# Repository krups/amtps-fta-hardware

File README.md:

# amtps-fta
Design files for the additive manufacturing thermal of thermal protection systems (AMTPS) flight test article (FTA)

See [documentation/amtps-fta-harware-manual.pdf](documentation/amtps-fta-harware-manual.pdf)

For an overview of the work, see the presentation here [documentation/presentation.pdf](documentation/presentation.pdf)

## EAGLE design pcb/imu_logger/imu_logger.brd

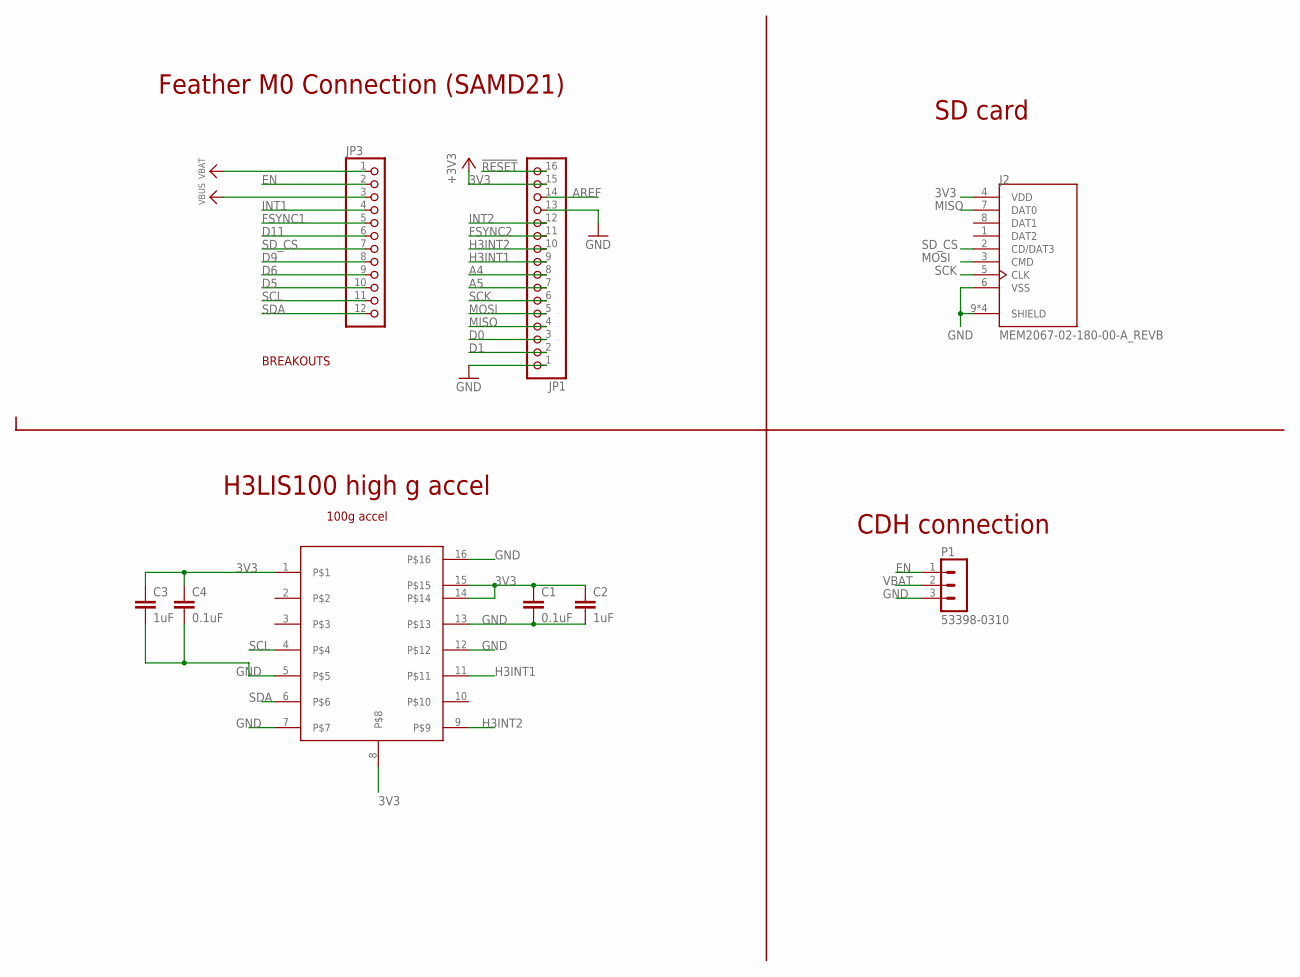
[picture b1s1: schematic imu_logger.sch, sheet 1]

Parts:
C1, C4: 0.1uF; C0603
C2, C3: 1uF; C0603
J2: MEM2067-02-180-00-A_REVB; GCT_MEM2067-02-180-00-A_REVB
JP1: HEADER-1X16ROUND; 1X16_ROUND
JP3: HEADER-1X12; 1X12_ROUND
P1: 53398-0310
U$1: H3LIS100DL; XDCR_LIS3DHTR

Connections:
3V3: C1.1, C2.1, C3.1, C4.1, J2.4 (VDD), JP1.15, U$1.1, U$1.8, U$1.14, U$1.15; also elsewhere on the board
!RESET: JP1.16
A4: JP1.8
A5: JP1.7
AREF: JP1.14
D0: JP1.3
D1: JP1.2
D5: JP3.10
D6: JP3.9
D9: JP3.8
D11: JP3.6
EN: JP3.2, P1.1; also elsewhere on the board
FSYNC1: JP3.5; also elsewhere on the board
FSYNC2: JP1.11; also elsewhere on the board
GND: C1.2, C2.2, C3.2, C4.2, J2.6 (VSS), J2.9 (SHIELD), J2.10 (SHIELD), J2.11 (SHIELD), J2.12 (SHIELD), JP1.1, JP1.13, P1.3, U$1.5, U$1.7, U$1.12, U$1.13, U$1.16; also elsewhere on the board
H3INT1: JP1.9, U$1.11
H3INT2: JP1.10, U$1.9
INT1: JP3.4; also elsewhere on the board
INT2: JP1.12; also elsewhere on the board
MISO: J2.7 (DAT0), JP1.4
MOSI: J2.3 (CMD), JP1.5
SCK: J2.5 (CLK), JP1.6
SCL: JP3.11, U$1.4; also elsewhere on the board
SDA: JP3.12, U$1.6; also elsewhere on the board
SD_CS: J2.2 (CD/DAT3), JP3.7
VBAT: JP3.1, P1.2; also elsewhere on the board
VBUS: JP3.3

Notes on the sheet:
BREAKOUTS
100g accel
CDH connection
SD card
Feather M0 Connection (SAMD21)
H3LIS100 high g accel

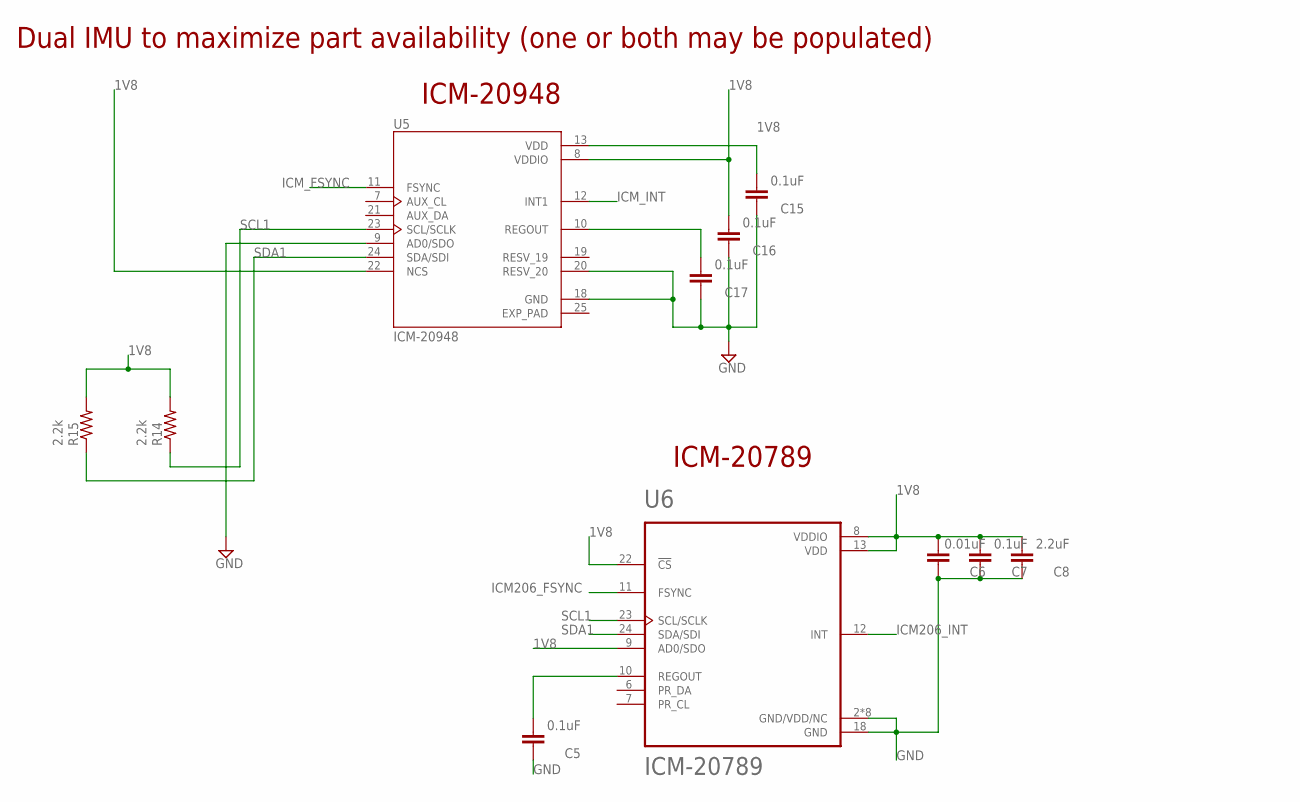
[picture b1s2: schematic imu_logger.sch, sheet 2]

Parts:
C5, C7, C15, C16, C17: 0.1uF; C0603
C6: 0.01uF; C0603
C8: 2.2uF; C0603
R14, R15: 2.2k; R0603
U5: ICM-20948; QFN40P300X300X105-25N
U6: ICM-20789; PQFN50P400X400X146-24N

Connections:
1V8: C6.2, C7.2, C8.2, C15.2, C16.2, R14.2, R15.2, U5.8 (VDDIO), U5.13 (VDD), U5.22 (NCS), U6.8 (VDDIO), U6.9 (AD0/SDO), U6.13 (VDD), U6.22 (!CS); also elsewhere on the board
EXP_PAD: U5.25 (EXP_PAD)
GND: C5.1, C6.1, C7.1, C8.1, C15.1, C16.1, C17.1, U5.9 (AD0/SDO), U5.18 (GND), U5.20 (RESV_20), U6.2 (GND/VDD/NC), U6.3 (GND/VDD/NC), U6.4 (GND/VDD/NC), U6.5 (GND/VDD/NC), U6.14 (GND/VDD/NC), U6.15 (GND/VDD/NC), U6.16 (GND/VDD/NC), U6.17 (GND/VDD/NC), U6.18 (GND); also elsewhere on the board
ICM206_FSYNC: U6.11 (FSYNC); also elsewhere on the board
ICM206_INT: U6.12 (INT); also elsewhere on the board
ICM_FSYNC: U5.11 (FSYNC); also elsewhere on the board
ICM_INT: U5.12 (INT1); also elsewhere on the board
unnamed: C5.2, U6.10 (REGOUT)
unnamed: C17.2, U5.10 (REGOUT)
SCL1: R14.1, U5.23 (SCL/SCLK), U6.23 (SCL/SCLK); also elsewhere on the board
SDA1: R15.1, U5.24 (SDA/SDI), U6.24 (SDA/SDI); also elsewhere on the board

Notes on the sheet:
Dual IMU to maximize part availability (one or both may be populated)
ICM-20948
ICM-20789

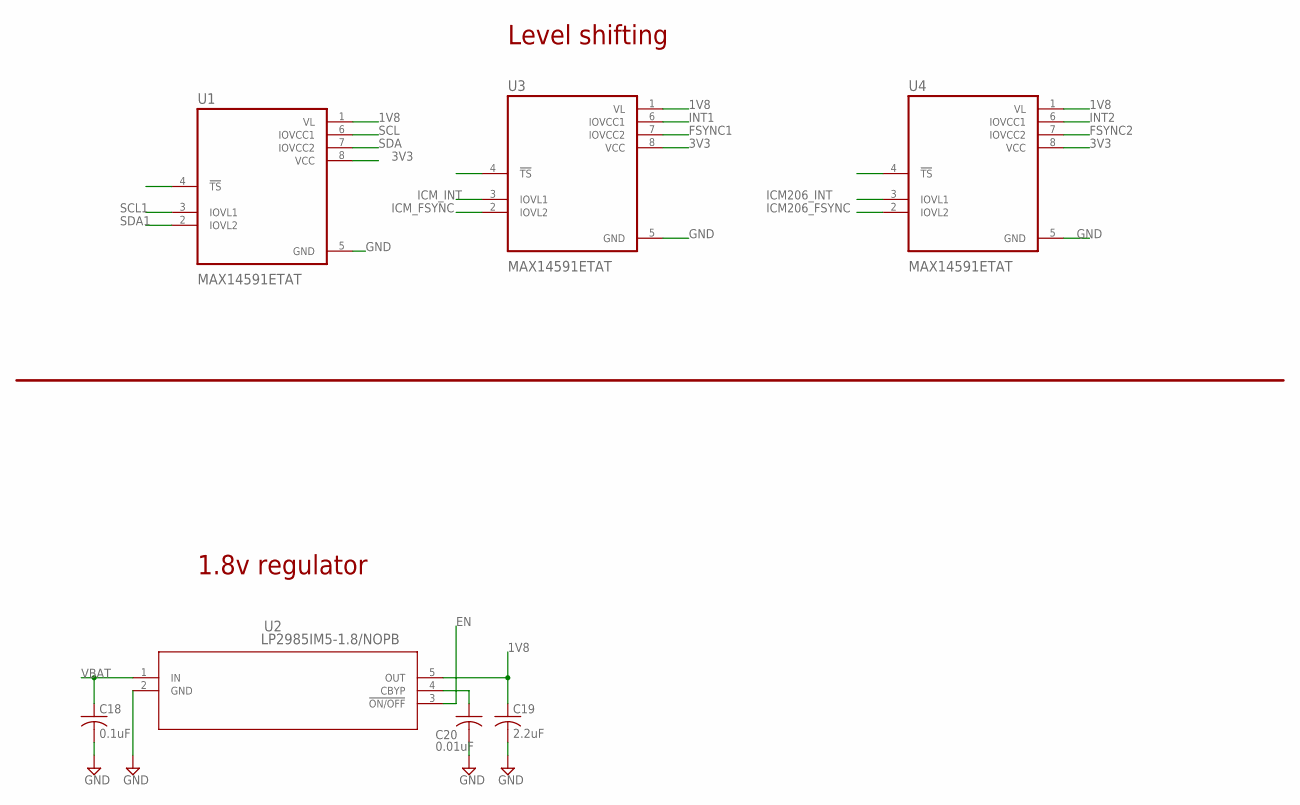
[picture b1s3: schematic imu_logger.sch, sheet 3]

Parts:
C18: 0.1uF; C0603
C19: 2.2uF; C0603
C20: 0.01uF; C0603
U1, U3, U4: MAX14591ETAT; SON50P200X200X80-8N
U2: LP2985IM5-1.8/NOPB; MF05A

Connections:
1V8: C19.1, U1.1 (VL), U2.5 (OUT), U3.1 (VL), U4.1 (VL); also elsewhere on the board
3V3: U1.8 (VCC), U3.8 (VCC), U4.8 (VCC); also elsewhere on the board
EN: U2.3 (!ON/OFF); also elsewhere on the board
FSYNC1: U3.7 (IOVCC2); also elsewhere on the board
FSYNC2: U4.7 (IOVCC2); also elsewhere on the board
GND: C18.2, C19.2, C20.2, U1.5 (GND), U2.2 (GND), U3.5 (GND), U4.5 (GND); also elsewhere on the board
ICM206_FSYNC: U4.2 (IOVL2); also elsewhere on the board
ICM206_INT: U4.3 (IOVL1); also elsewhere on the board
ICM_FSYNC: U3.2 (IOVL2); also elsewhere on the board
ICM_INT: U3.3 (IOVL1); also elsewhere on the board
INT1: U3.6 (IOVCC1); also elsewhere on the board
INT2: U4.6 (IOVCC1); also elsewhere on the board
unnamed: C20.1, U2.4 (CBYP)
SCL: U1.6 (IOVCC1); also elsewhere on the board
SCL1: U1.3 (IOVL1); also elsewhere on the board
SDA: U1.7 (IOVCC2); also elsewhere on the board
SDA1: U1.2 (IOVL2); also elsewhere on the board
VBAT: C18.1, U2.1 (IN); also elsewhere on the board

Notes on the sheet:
Level shifting
1.8v regulator

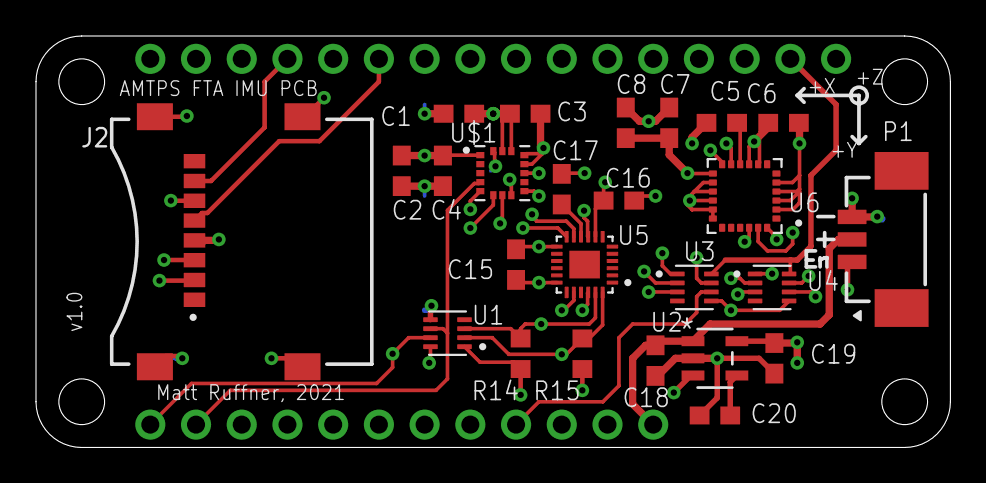
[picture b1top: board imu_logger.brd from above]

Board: 4 copper layers, 50.8 x 22.9 mm, 27 parts (0 on the bottom side), 26 nets.

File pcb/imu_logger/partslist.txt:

Partlist

Exported from imu_logger.sch at 10/19/21 1:54 PM

EAGLE Version 9.6.2 Copyright (c) 1988-2020 Autodesk, Inc.

Assembly variant: 

Part     Value              Device             Package                Library             Sheet

C1       0.1uF              C-EUC0603          C0603                  rcl                 1
C2       1uF                C-EUC0603          C0603                  rcl                 1
C3       1uF                C-EUC0603          C0603                  rcl                 1
C4       0.1uF              C-EUC0603          C0603                  rcl                 1
C5       0.1uF              C-EUC0603          C0603                  rcl                 2
C6       0.01uF             C-EUC0603          C0603                  rcl                 2
C7       0.1uF              C-EUC0603          C0603                  rcl                 2
C8       2.2uF              C-EUC0603          C0603                  rcl                 2
C15      0.1uF              C-EUC0603          C0603                  rcl                 2
C16      0.1uF              C-EUC0603          C0603                  rcl                 2
C17      0.1uF              C-EUC0603          C0603                  rcl                 2
C18      0.1uF              C-USC0603          C0603                  rcl                 3
C19      2.2uF              C-USC0603          C0603                  rcl                 3
C20      0.01uF             C-USC0603          C0603                  rcl                 3
J1       DM3CS-SF           DM3CS-SF           HRS_DM3CS-SF           DM3CS-SF            1
JP1                         HEADER-1X16ROUND   1X16_ROUND             microbuilder        1
JP3                         HEADER-1X12        1X12_ROUND             microbuilder        1
P1       53398-0310         53398-0310         53398-0310             con-molex-picoblade 1
R14      2.2k               R-US_R0603         R0603                  rcl                 2
R15      2.2k               R-US_R0603         R0603                  rcl                 2
U$1      H3LIS100DL         H3LIS100DL         XDCR_LIS3DHTR          LIS3DHTR            1
U1       MAX14591ETAT       MAX14591ETAT       SON50P200X200X80-8N    MAX14591ETAT        3
U2       LP2985IM5-1.8/NOPB LP2985IM5-1.8/NOPB MF05A                  gsynth              3
U3       MAX14591ETAT       MAX14591ETAT       SON50P200X200X80-8N    MAX14591ETAT        3
U4       MAX14591ETAT       MAX14591ETAT       SON50P200X200X80-8N    MAX14591ETAT        3
U5       ICM-20948          ICM-20948          QFN40P300X300X105-25N  ICM-20948           2
U6       ICM-20789          ICM-20789          PQFN50P400X400X146-24N ICM-20789           2

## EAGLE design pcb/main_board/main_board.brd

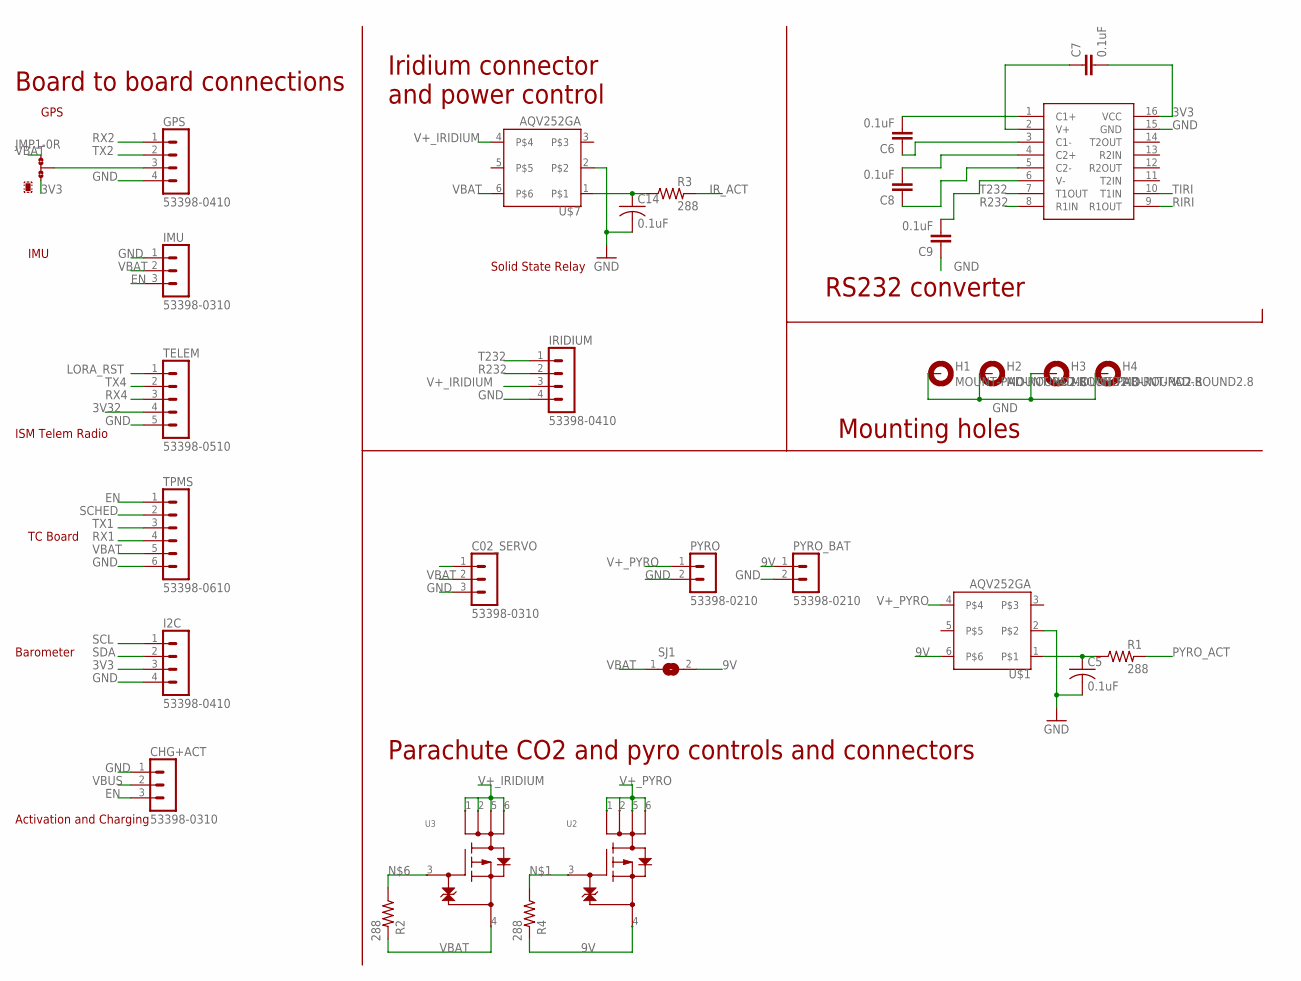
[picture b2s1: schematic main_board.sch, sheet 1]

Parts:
C02_SERVO: 53398-0310
C5, C6, C7, C8, C9, C14: 0.1uF; C0603
CHG+ACT: 53398-0310
GPS: 53398-0410
H1, H2, H3, H4: MOUNT-PAD-ROUND2.8; 2,8-PAD
I2C: 53398-0410
IMU: 53398-0310
IRIDIUM: 53398-0410
JMP1: 0R-JUMPA; A0R-JMP
PYRO: 53398-0210
PYRO_BAT: 53398-0210
R1, R2, R3, R4: 288; R0603
SJ1: SJ
TELEM: 53398-0510
TPMS: 53398-0610
U2, U3: SSM6J414TU; UF6_TOS
U$1, U$7: AQV252GA; DIP6
U$2: UM3232EEAE; RQ_16_ADI

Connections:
3V3: C7.2, I2C.3, JMP1.3, U$2.16 (VCC); also elsewhere on the board
3V32: TELEM.4; also elsewhere on the board
9V: PYRO_BAT.1, R4.2, SJ1.2, U2.4, U$1.6
CO2_SERVO: C02_SERVO.1; also elsewhere on the board
EN: CHG+ACT.3, IMU.3, TPMS.1; also elsewhere on the board
GND: C02_SERVO.3, C5.2, C9.1, C14.2, CHG+ACT.1, GPS.4, H1.B2,8, H2.B2,8, H3.B2,8, H4.B2,8, I2C.4, IMU.1, IRIDIUM.4, PYRO.2, PYRO_BAT.2, TELEM.5, TPMS.6, U$1.2, U$2.15 (GND), U$7.2; also elsewhere on the board
IR_ACT: R3.2; also elsewhere on the board
LORA_RST: TELEM.1; also elsewhere on the board
unnamed: C5.1, R1.1, R4.1, U2.3, U$1.1
unnamed: GPS.3, JMP1.2
unnamed: C6.2, U$2.1 (C1+)
unnamed: C14.1, R2.1, R3.1, U3.3, U$7.1
unnamed: C7.1, U$2.2 (V+)
unnamed: C6.1, U$2.3 (C1-)
unnamed: C8.2, U$2.4 (C2+)
unnamed: C8.1, U$2.5 (C2-)
unnamed: C9.2, U$2.6 (V-)
PYRO_ACT: R1.2; also elsewhere on the board
R232: IRIDIUM.2, U$2.8 (R1IN)
RIRI: U$2.9 (R1OUT); also elsewhere on the board
RX1: TPMS.4; also elsewhere on the board
RX2: GPS.1; also elsewhere on the board
RX4: TELEM.3; also elsewhere on the board
SCHED: TPMS.2; also elsewhere on the board
SCL: I2C.1; also elsewhere on the board
SDA: I2C.2; also elsewhere on the board
T232: IRIDIUM.1, U$2.7 (T1OUT)
TIRI: U$2.10 (T1IN); also elsewhere on the board
TX1: TPMS.3; also elsewhere on the board
TX2: GPS.2; also elsewhere on the board
TX4: TELEM.2; also elsewhere on the board
V+_IRIDIUM: IRIDIUM.3, U3.1, U3.2, U3.5, U3.6, U$7.4
V+_PYRO: PYRO.1, U2.1, U2.2, U2.5, U2.6, U$1.4
VBAT: C02_SERVO.2, IMU.2, JMP1.1, R2.2, SJ1.1, TPMS.5, U3.4, U$7.6; also elsewhere on the board
VBUS: CHG+ACT.2; also elsewhere on the board

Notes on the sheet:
GPS
TC Board
Solid State Relay
Board to board connections
IMU
ISM Telem Radio
Barometer
Activation and Charging
Iridium connector and power control
RS232 converter
Mounting holes
Parachute CO2 and pyro controls and connectors

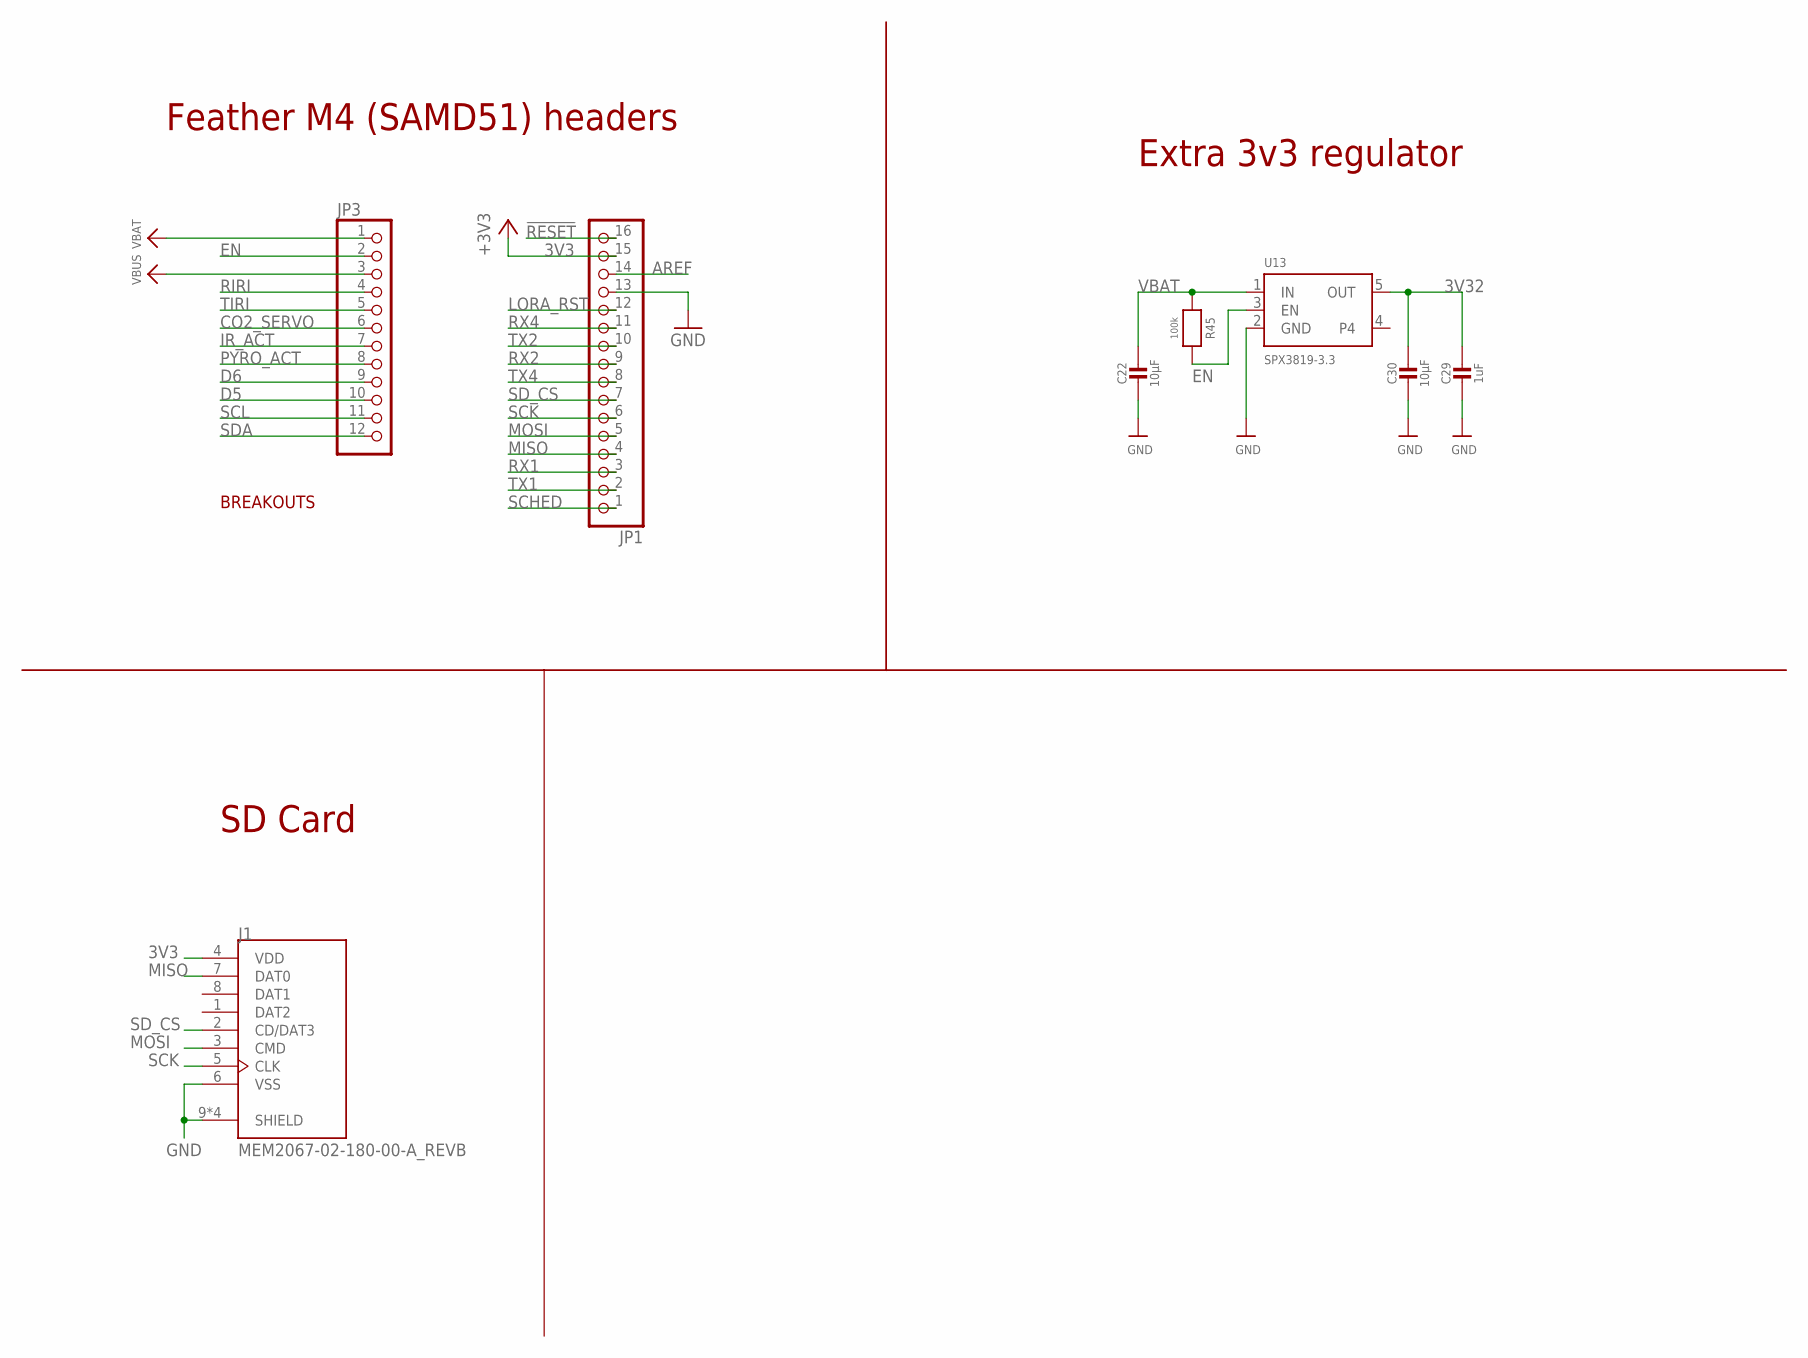
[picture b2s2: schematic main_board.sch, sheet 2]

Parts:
C22, C30: 10µF; 0805-NO
C29: 1uF; 0603-NO
J1: MEM2067-02-180-00-A_REVB; GCT_MEM2067-02-180-00-A_REVB
JP1: HEADER-1X16ROUND; 1X16_ROUND
JP3: HEADER-1X12; 1X12_ROUND
R45: 100k; 0603-NO
U13: SPX3819-3.3; SOT23-5

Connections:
3V3: J1.4 (VDD), JP1.15; also elsewhere on the board
3V32: C29.1, C30.1, U13.5 (OUT); also elsewhere on the board
!RESET: JP1.16
AREF: JP1.14
CO2_SERVO: JP3.6; also elsewhere on the board
D5: JP3.10
D6: JP3.9
EN: JP3.2, R45.2, U13.3 (EN); also elsewhere on the board
GND: C22.2, C29.2, C30.2, J1.6 (VSS), J1.9 (SHIELD), J1.10 (SHIELD), J1.11 (SHIELD), J1.12 (SHIELD), JP1.13, U13.2 (GND); also elsewhere on the board
IR_ACT: JP3.7; also elsewhere on the board
LORA_RST: JP1.12; also elsewhere on the board
MISO: J1.7 (DAT0), JP1.4
MOSI: J1.3 (CMD), JP1.5
PYRO_ACT: JP3.8; also elsewhere on the board
RIRI: JP3.4; also elsewhere on the board
RX1: JP1.3; also elsewhere on the board
RX2: JP1.9; also elsewhere on the board
RX4: JP1.11; also elsewhere on the board
SCHED: JP1.1; also elsewhere on the board
SCK: J1.5 (CLK), JP1.6
SCL: JP3.11; also elsewhere on the board
SDA: JP3.12; also elsewhere on the board
SD_CS: J1.2 (CD/DAT3), JP1.7
TIRI: JP3.5; also elsewhere on the board
TX1: JP1.2; also elsewhere on the board
TX2: JP1.10; also elsewhere on the board
TX4: JP1.8; also elsewhere on the board
VBAT: C22.1, JP3.1, R45.1, U13.1 (IN); also elsewhere on the board
VBUS: JP3.3; also elsewhere on the board

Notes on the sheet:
BREAKOUTS
Feather M4 (SAMD51) headers
Extra 3v3 regulator
SD Card

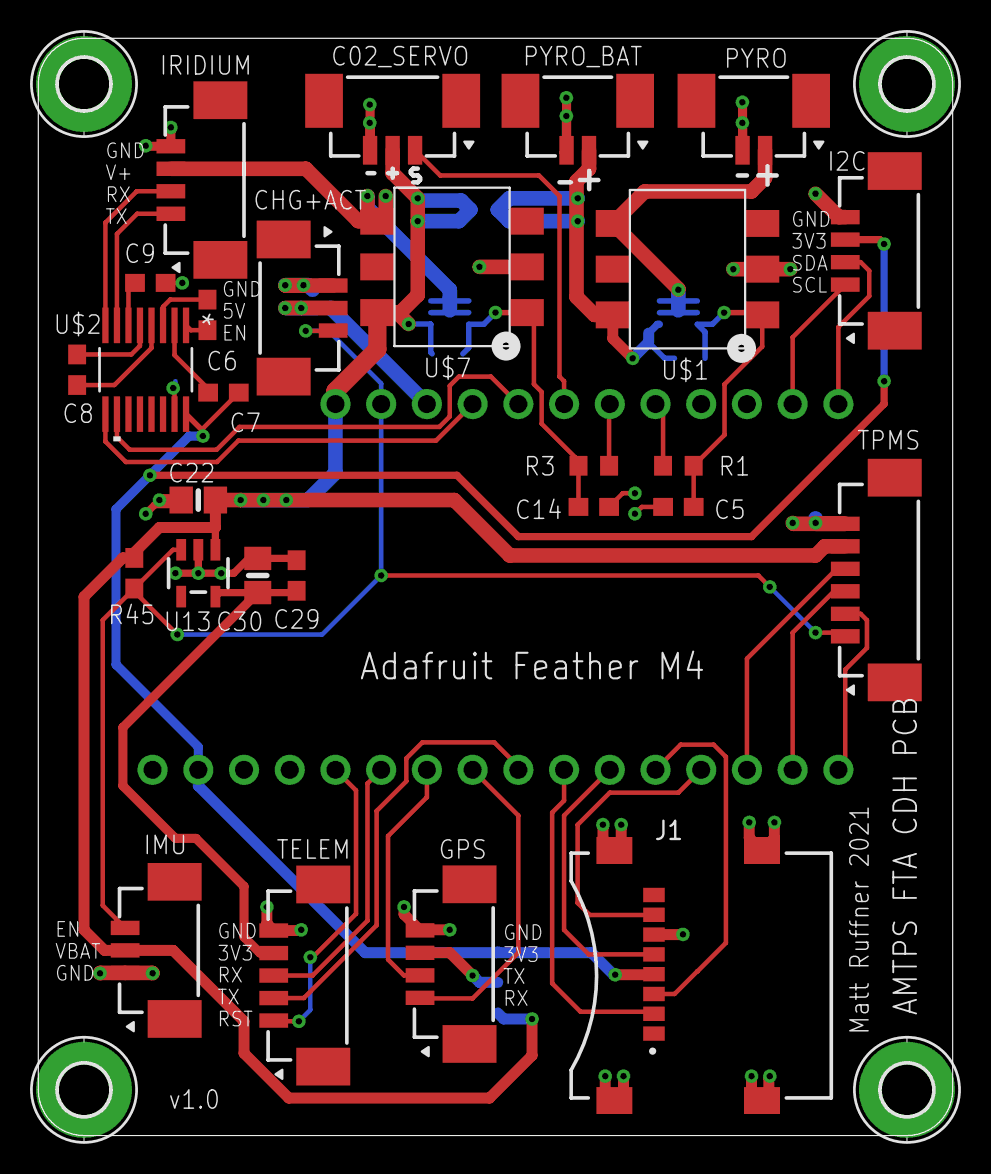
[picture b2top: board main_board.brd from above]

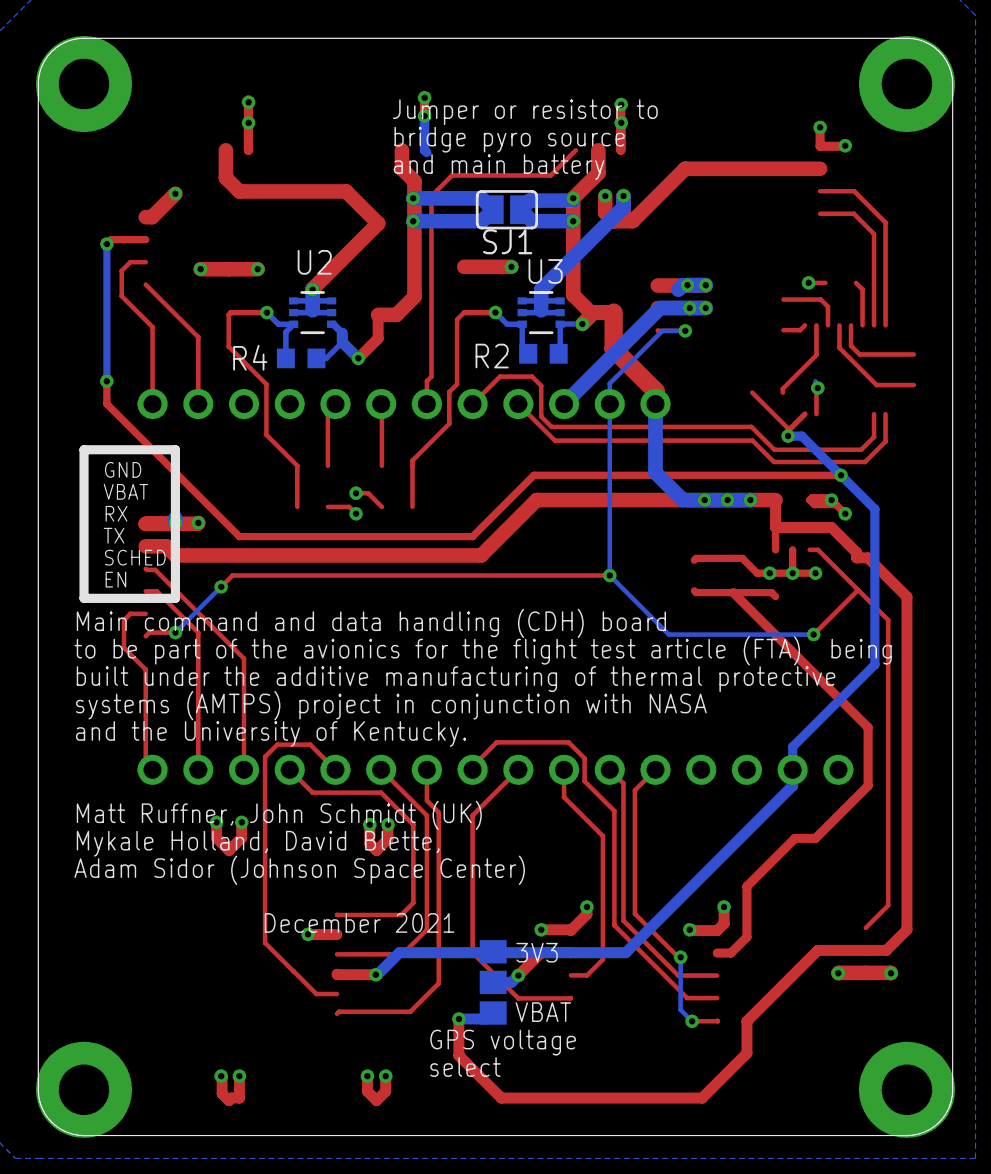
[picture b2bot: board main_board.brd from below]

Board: 4 copper layers, 50.8 x 61.0 mm, 39 parts (6 on the bottom side), 39 nets.

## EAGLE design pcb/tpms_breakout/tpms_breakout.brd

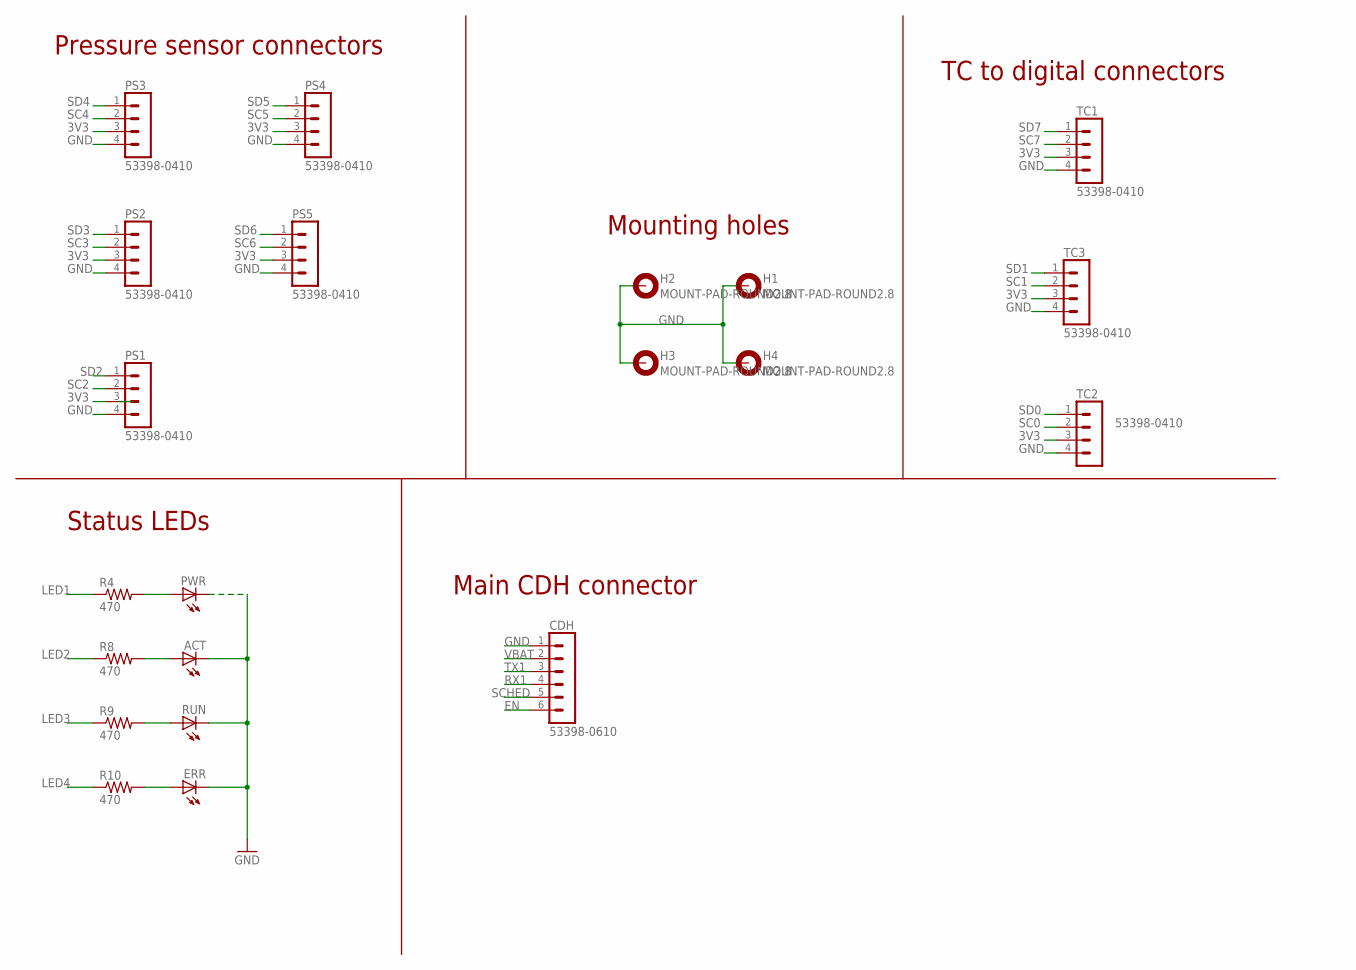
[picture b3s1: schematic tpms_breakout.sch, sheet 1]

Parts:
ACT: LEDCHIP-LED0603; CHIP-LED0603
CDH: 53398-0610
ERR: LEDCHIP-LED0603; CHIP-LED0603
H1, H2, H3, H4: MOUNT-PAD-ROUND2.8; 2,8-PAD
PS1, PS2, PS3, PS4, PS5: 53398-0410
PWR: LEDCHIP-LED0603; CHIP-LED0603
R4, R8, R9, R10: 470; R0603
RUN: LEDCHIP-LED0603; CHIP-LED0603
TC1, TC2, TC3: 53398-0410

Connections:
3V3: PS1.3, PS2.3, PS3.3, PS4.3, PS5.3, TC1.3, TC2.3, TC3.3; also elsewhere on the board
EN: CDH.6; also elsewhere on the board
GND: ACT.C, CDH.1, ERR.C, H1.B2,8, H2.B2,8, H3.B2,8, H4.B2,8, PS1.4, PS2.4, PS3.4, PS4.4, PS5.4, PWR.C, RUN.C, TC1.4, TC2.4, TC3.4; also elsewhere on the board
LED1: R4.1; also elsewhere on the board
LED2: R8.1; also elsewhere on the board
LED3: R9.1; also elsewhere on the board
LED4: R10.1; also elsewhere on the board
unnamed: PWR.A, R4.2
unnamed: ACT.A, R8.2
unnamed: R9.2, RUN.A
unnamed: ERR.A, R10.2
RX1: CDH.4; also elsewhere on the board
SC0: TC2.2; also elsewhere on the board
SC1: TC3.2; also elsewhere on the board
SC2: PS1.2; also elsewhere on the board
SC3: PS2.2; also elsewhere on the board
SC4: PS3.2; also elsewhere on the board
SC5: PS4.2; also elsewhere on the board
SC6: PS5.2; also elsewhere on the board
SC7: TC1.2; also elsewhere on the board
SCHED: CDH.5; also elsewhere on the board
SD0: TC2.1; also elsewhere on the board
SD1: TC3.1; also elsewhere on the board
SD2: PS1.1; also elsewhere on the board
SD3: PS2.1; also elsewhere on the board
SD4: PS3.1; also elsewhere on the board
SD5: PS4.1; also elsewhere on the board
SD6: PS5.1; also elsewhere on the board
SD7: TC1.1; also elsewhere on the board
TX1: CDH.3; also elsewhere on the board
VBAT: CDH.2; also elsewhere on the board

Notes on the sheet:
Pressure sensor connectors
Mounting holes
TC to digital connectors
Main CDH connector
Status LEDs

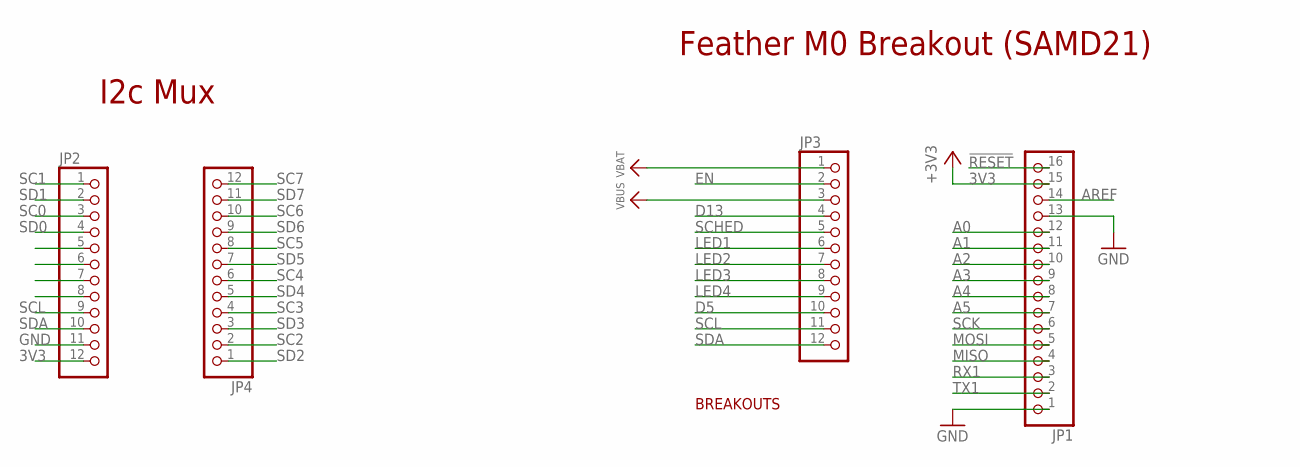
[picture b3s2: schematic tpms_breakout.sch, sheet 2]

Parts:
JP1: HEADER-1X16ROUND; 1X16_ROUND
JP2, JP3, JP4: HEADER-1X12; 1X12_ROUND

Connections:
3V3: JP1.15, JP2.12; also elsewhere on the board
!RESET: JP1.16
A0: JP1.12
A1: JP1.11
A2: JP1.10
A3: JP1.9
A4: JP1.8
A5: JP1.7
AREF: JP1.14
D5: JP3.10
D13: JP3.4
EN: JP3.2; also elsewhere on the board
GND: JP1.1, JP1.13, JP2.11; also elsewhere on the board
LED1: JP3.6; also elsewhere on the board
LED2: JP3.7; also elsewhere on the board
LED3: JP3.8; also elsewhere on the board
LED4: JP3.9; also elsewhere on the board
MISO: JP1.4
MOSI: JP1.5
RX1: JP1.3; also elsewhere on the board
SC0: JP2.3; also elsewhere on the board
SC1: JP2.1; also elsewhere on the board
SC2: JP4.2; also elsewhere on the board
SC3: JP4.4; also elsewhere on the board
SC4: JP4.6; also elsewhere on the board
SC5: JP4.8; also elsewhere on the board
SC6: JP4.10; also elsewhere on the board
SC7: JP4.12; also elsewhere on the board
SCHED: JP3.5; also elsewhere on the board
SCK: JP1.6
SCL: JP2.9, JP3.11
SD0: JP2.4; also elsewhere on the board
SD1: JP2.2; also elsewhere on the board
SD2: JP4.1; also elsewhere on the board
SD3: JP4.3; also elsewhere on the board
SD4: JP4.5; also elsewhere on the board
SD5: JP4.7; also elsewhere on the board
SD6: JP4.9; also elsewhere on the board
SD7: JP4.11; also elsewhere on the board
SDA: JP2.10, JP3.12
TX1: JP1.2; also elsewhere on the board
VBAT: JP3.1; also elsewhere on the board
VBUS: JP3.3

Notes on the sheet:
BREAKOUTS
I2c Mux
Feather M0 Breakout (SAMD21)

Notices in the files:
parts and their libraries:
con-molex-picoblade: Copyright (C) 2010, Bob Starr
COPYRIGHT: Copyright (C) 2018 Accelerated Designs. All rights reserved
microbuilder: This work is placed in the public domain, and may be freely used for commercial and non-commercial work with the following conditions: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
